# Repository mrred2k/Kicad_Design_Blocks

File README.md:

# KiCad Design Blocks

Stop redrawing the same 3V3 LDO, the same USB-C receptacle and the same buck
converter in every new project.

This repository collects those fragments as **design blocks**: a schematic you drop
into your sheet, plus — where available — the matching PCB layout, with footprints,
values and LCSC part numbers already assigned. Add the repo as a Git submodule, point
KiCad at it, and the blocks show up in the Design Block palette of the Schematic and
PCB editors.

## Requirements

| | |
|---|---|
| **KiCad** | 10.0 or newer. Schematic design blocks arrived in KiCad 9, PCB design blocks in KiCad 10 — this library uses both. |
| **Git** | Anything that supports submodules. |

## Using the blocks in a project

### 1. Add the library once

```bash
git submodule add https://github.com/mrred2k/Kicad_Design_Blocks.git kicad-design-blocks
git commit -m "Add kicad-design-blocks submodule"
```

### 2. Point KiCad at it

**Preferences → Manage Design Block Libraries → Add:**

| Nickname | Path |
|----------|------|
| `blocks` | `${KIPRJMOD}/kicad-design-blocks/blocks.kicad_blocks` |

This writes a `design-block-lib-table` into your project folder — commit it, so the
next person cloning your project gets the same library binding.

### 3. Place a block

Open the **Design Blocks** panel (Schematic Editor, right dock), pick a block, click
the canvas. Most blocks arrive with reference designators already unique-ish and with
hidden power symbols; reconnect `+3V3`, `+5V`, `GND` and the I/O labels to your own
nets.

PCB blocks live in the PCB Editor's Design Blocks panel. Place the schematic part
first, then the layout inside the same project so both stay in sync.

### Clone a project that already uses this library

```bash
git clone --recurse-submodules <project-url>
# already cloned?
git submodule update --init
```

### Pull new blocks into an existing project

```bash
git submodule update --remote kicad-design-blocks
git add kicad-design-blocks
git commit -m "Update kicad-design-blocks"
```

## What is inside a block

```
blocks.kicad_blocks/
└── <BlockName>.kicad_block/
    ├── <BlockName>.kicad_sch    # Schematic fragment
    ├── <BlockName>.kicad_pcb    # PCB layout fragment (optional)
    ├── <BlockName>.json         # Description, keywords, metadata fields
    ├── <BlockName>_preview.svg  # Generated by CI
    └── README.md                # Generated by CI (BOM + badges)
```

The `.json` is the contract: `description` and `keywords` are what KiCad shows in the
block browser, and the metadata fields decide the quality tier
([quality scale](CONTRIBUTING.md#quality-scale)):

| Field | Meaning |
|-------|---------|
| `maturity` | `schematic` → `layout` → `produced` |
| `lcsc_parts` | LCSC part numbers assigned to every component |
| `jlcpcb_basic` | Parts picked from the JLCPCB Basic list where possible |
| `has_3d` | 3D models assigned (`yes` / `partial` / `no`) |
| `reviewed` | Second pair of eyes looked at it |

A **Silver** block is the usual target: layout included, LCSC numbers everywhere, no
JLCPCB Extended-part surcharges.

## Contributing a block

1. In the Schematic Editor: select the circuit → right click → **Save as Design Block**
2. Choose the `blocks` library, fill in name, keywords, description and metadata
3. Optionally save the matching PCB layout as a design block in the PCB Editor
4. Open a pull request

CI then renders your block, posts the preview and a BOM as a PR comment, and flags
metadata problems. Full details: [CONTRIBUTING.md](CONTRIBUTING.md).

## Automation

Nothing in this repo is drawn by hand twice. Three workflows keep it consistent:

| Workflow | Trigger | What it does |
|----------|---------|--------------|
| **Validate design blocks** | PR touching `blocks.kicad_blocks/` | Checks every block has schematic, `.json`, description and valid metadata |
| **PR block preview** | PR touching `blocks.kicad_blocks/` | Renders new/changed blocks, posts preview + BOM + JLCPCB hints as a PR comment |
| **Generate block previews** | push to `main` | Re-renders every block preview and refreshes the per-block README + BOM, commits the result |

## KiCad documentation

- [Schematic design blocks](https://docs.kicad.org/10.0/en/eeschema/eeschema.html#schematic-design-blocks)
- [PCB design blocks](https://docs.kicad.org/10.0/en/pcbnew/pcbnew.html#pcb-design-blocks)

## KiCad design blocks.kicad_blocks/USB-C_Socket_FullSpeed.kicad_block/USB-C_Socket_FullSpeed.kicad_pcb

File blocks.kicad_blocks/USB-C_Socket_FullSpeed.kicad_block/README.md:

<!-- AUTO-GENERATED — do not edit, this file is overwritten on every push to main -->

# USB-C_Socket_FullSpeed

USB 2.0 Type-C receptacle for full-speed devices (HRO TYPE-C-31-M-12), 5.1k pulldowns on CC1/CC2 for 5V sink, 3.6V zener clamps on D+/D-. No 1.5k data pull-up: full-speed devices with an internal pull-up (CH340, RP2040, STM32) connect directly. Socket and ESD are LCSC Extended (no Basic alternative exists in the JLC catalogue); the CC resistors are Basic. Layout included. Superseded by USB-C_Socket_FullSpeed_SRV05, which uses an SRV05-4 array instead of the zeners (roughly 300x lower line capacitance, nanosecond clamping, also protects CC1/CC2); kept as the simpler variant when a zener is acceptable.

## Bill of Materials

*Manufacturer, MPN and JLCPCB class fetched automatically from the [JLCPCB parts API](https://jlcpcb.com/parts).*

| Refs | Value | Footprint | LCSC | JLCPCB | Manufacturer | MPN | Category |
| --- | --- | --- | --- | --- | --- | --- | --- |
| D7, D8 | 3.6V | D_SOD-123 | C22395524 | Extended | hongjiacheng | MM1W3V6 | Zener Diodes |
| J2 | TYPE-C-31-M-12 | USB_C_Receptacle_HRO_TYPE-C-31-M-12 | C165948 | Extended | Korean Hroparts Elec | TYPE-C-31-M-12 | USB Connectors |
| R11, R13 | 5.1k | R_0603_1608Metric | C23186 | Basic | UNI-ROYAL(Uniroyal Elec) | 0603WAF5101T5E | Chip Resistor - Surface Mount |

---
*Keywords: usb usb-c type-c connector full-speed sink cc-resistor esd*

| | |
|---|---|
| Maturity | Layout |
| LCSC Parts | Yes |
| JLCPCB | Optimized for Basic Parts |
| 3D Models | Partial |
| Reviewed | No |

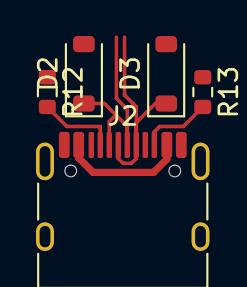
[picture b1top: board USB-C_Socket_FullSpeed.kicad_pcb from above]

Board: 2 copper layers, 5 parts (0 on the bottom side), 6 nets.

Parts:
D2, D3: 3.6V; D_SOD-123
J2: TYPE-C-31-M-12; USB_C_Receptacle_HRO_TYPE-C-31-M-12
R12, R13: 5.1k; R_0603_1608Metric

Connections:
+5V: J2.A4 (VBUS), J2.A9 (VBUS), J2.B4 (VBUS), J2.B9 (VBUS)
GND: D2.2 (A), D3.2 (A), J2.A1 (GND), J2.A12 (GND), J2.B1 (GND), J2.B12 (GND), J2.SH (SHIELD), R12.1, R13.1
unnamed: J2.A5 (CC1), R12.2
unnamed: J2.B5 (CC2), R13.2
USD_D+: D3.1 (K), J2.A6 (D+), J2.B6 (D+)
USD_D-: D2.1 (K), J2.A7 (D-), J2.B7 (D-)

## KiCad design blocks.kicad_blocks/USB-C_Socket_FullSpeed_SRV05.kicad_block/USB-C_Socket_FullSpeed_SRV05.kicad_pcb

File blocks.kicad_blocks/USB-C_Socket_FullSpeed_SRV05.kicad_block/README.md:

<!-- AUTO-GENERATED — do not edit, this file is overwritten on every push to main -->

# USB-C_Socket_FullSpeed_SRV05

USB 2.0 Type-C receptacle (HRO TYPE-C-31-M-12) as a 5V sink for full-speed devices: 5.1k pulldowns on CC1/CC2, ESD array SRV05-4 (SOT-23-6, 0.3 pF, 4 channels) protecting D+, D-, CC1 and CC2, VP tied to VBUS (5V), VN to GND. No 1.5k data pull-up - full-speed devices with an internal pull-up (CH340, RP2040, STM32) connect directly. Preferred over USB-C_Socket_FullSpeed, which uses two 3.6V zeners: the array has roughly 300x lower line capacitance, clamps in nanoseconds instead of microseconds and also protects the CC lines. Socket and ESD array are LCSC Extended (the JLC catalogue has no Basic ESD part); the 5.1k resistors are Basic. Schematic and layout included; the USB-C footprint lives in the project library GnssFanout, so the block is used inside projects of this repo family.

## Bill of Materials

*Manufacturer, MPN and JLCPCB class fetched automatically from the [JLCPCB parts API](https://jlcpcb.com/parts).*

| Refs | Value | Footprint | LCSC | JLCPCB | Manufacturer | MPN | Category |
| --- | --- | --- | --- | --- | --- | --- | --- |
| J2 | TYPE-C-31-M-12 | USB_C_Receptacle_HRO_TYPE-C-31-M-12 | C165948 | Extended | Korean Hroparts Elec | TYPE-C-31-M-12 | USB Connectors |
| R11, R13 | 5.1k | R_0603_1608Metric | C23186 | Basic | UNI-ROYAL(Uniroyal Elec) | 0603WAF5101T5E | Chip Resistor - Surface Mount |
| U6 | SRV05-4 | SOT-23-6 | C558418 | Extended | TECH PUBLIC | SRV05-4 | ESD and Surge Protection (TVS/ESD) |

---
*Keywords: usb usb-c type-c connector full-speed 5v sink cc-resistor esd srv05 tvs*

| | |
|---|---|
| Maturity | Layout |
| LCSC Parts | Yes |
| JLCPCB | Optimized for Basic Parts |
| 3D Models | Yes |
| Reviewed | No |

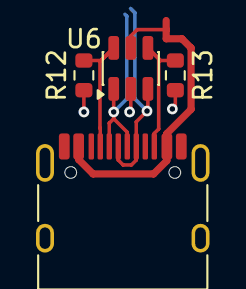
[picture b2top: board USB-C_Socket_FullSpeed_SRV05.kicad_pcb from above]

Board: 2 copper layers, 4 parts (0 on the bottom side), 6 nets.

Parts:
J2: TYPE-C-31-M-12; USB_C_Receptacle_HRO_TYPE-C-31-M-12
R12, R13: 5.1k; R_0603_1608Metric
U6: SRV05-4; SOT-23-6

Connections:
+5V: J2.A4 (VBUS), J2.A9 (VBUS), J2.B4 (VBUS), J2.B9 (VBUS), U6.5 (VP)
CC1: J2.A5 (CC1), R12.2, U6.6 (IO4)
CC2: J2.B5 (CC2), R13.2, U6.4 (IO3)
GND: J2.A1 (GND), J2.A12 (GND), J2.B1 (GND), J2.B12 (GND), J2.SH (SHIELD), R12.1, R13.1, U6.2 (VN)
USD_D+: J2.A6 (D+), J2.B6 (D+), U6.3 (IO2)
USD_D-: J2.A7 (D-), J2.B7 (D-), U6.1 (IO1)

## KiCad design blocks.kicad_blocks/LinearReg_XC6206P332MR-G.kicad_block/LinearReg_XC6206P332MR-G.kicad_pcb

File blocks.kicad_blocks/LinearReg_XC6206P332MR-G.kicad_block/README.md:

<!-- AUTO-GENERATED — do not edit, this file is overwritten on every push to main -->

# LinearReg_XC6206P332MR-G

LDO linear regulator, Vin 5V, Vout 3.3V fixed, 250mA max, XC6206P332MR-G (SOT-23-3)

## Bill of Materials

*Manufacturer, MPN and JLCPCB class fetched automatically from the [JLCPCB parts API](https://jlcpcb.com/parts).*

| Refs | Value | Footprint | LCSC | JLCPCB | Manufacturer | MPN | Category |
| --- | --- | --- | --- | --- | --- | --- | --- |
| C4 | 0.1u 50V | C_0603_1608Metric | C14663 | Basic | YAGEO | CC0603KRX7R9BB104 | Multilayer Ceramic Capacitors MLCC - SMD/SMT |
| C5, C6 | 10uF (50V) | C_1206_3216Metric | C13585 | Basic | Samsung Electro-Mechanics | CL31A106KBHNNNE | Multilayer Ceramic Capacitors MLCC - SMD/SMT |
| U2 | XC6206P332MR-G | SOT-23-3 | C5446 | Basic | Torex Semicon | XC6206P332MR-G | Voltage Regulators - Linear, Low Drop Out (LDO) Regulators |

---
*Keywords: ldo linear regulator 3V3*

| | |
|---|---|
| Maturity | Layout |
| LCSC Parts | Yes |
| JLCPCB | Optimized for Basic Parts |
| 3D Models | Yes |
| Reviewed | No |

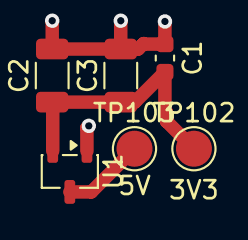
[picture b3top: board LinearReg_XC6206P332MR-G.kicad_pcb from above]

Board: 2 copper layers, 6 parts (0 on the bottom side), 3 nets.

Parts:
C1: 0.1u 50V; C_0603_1608Metric
C2, C3: 10uF (50V); C_1206_3216Metric
TP102: 3V3; TestPoint_Pad_D2.0mm
TP103: 5V; TestPoint_Pad_D2.0mm
U1: XC6206P332MR-G; SOT-23-3

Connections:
+3V3: C1.1, C2.1, C3.1, TP102.1, U1.2 (VO)
+5V: TP103.1, U1.3 (VI)
GND: C1.2, C2.2, C3.2, U1.1 (GND)

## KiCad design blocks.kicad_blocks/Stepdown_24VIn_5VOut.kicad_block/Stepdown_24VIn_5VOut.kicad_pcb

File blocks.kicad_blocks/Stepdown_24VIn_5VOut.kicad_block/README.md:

<!-- AUTO-GENERATED — do not edit, this file is overwritten on every push to main -->

# Stepdown_24VIn_5VOut

Buck (step-down) DC/DC converter, Vin max 32V, Vout fixed 5V

## Bill of Materials

*Manufacturer, MPN and JLCPCB class fetched automatically from the [JLCPCB parts API](https://jlcpcb.com/parts).*

| Refs | Value | Footprint | LCSC | JLCPCB | Manufacturer | MPN | Category |
| --- | --- | --- | --- | --- | --- | --- | --- |
| C406 | 0.1u 50V | C_0603_1608Metric | C14663 | Basic | YAGEO | CC0603KRX7R9BB104 | Multilayer Ceramic Capacitors MLCC - SMD/SMT |
| C407 | 100uF 35V | CP_Elec_6.3x5.4 | C2836442 | Extended | KNSCHA | RVT100UF35V67RV0034 | Aluminum Electrolytic Capacitors - SMD |
| C408 | 10uF (50V) | C_1206_3216Metric | C13585 | Basic | Samsung Electro-Mechanics | CL31A106KBHNNNE | Multilayer Ceramic Capacitors MLCC - SMD/SMT |
| C409, C410 | 47uF (10V) | C_1206_3216Metric_Pad1.33x1.80mm_HandSolder | C96123 | Basic | Samsung Electro-Mechanics | CL31A476MPHNNNE | Multilayer Ceramic Capacitors MLCC - SMD/SMT |
| L402 | 4.7uH | L_Sunlord_MWSA0503S | C177246 | Extended | cjiang (Changjiang Microelectronics Tech) | FXL0530-4R7-M | Molding Power Inductors |
| U402 | AP63205WU-7 | TSOT-23-6 | C2071056 | Extended | Diodes Incorporated | AP63205WU-7 | DC-DC Converters |

---
*Keywords: buck step-down dcdc converter 5V power*

| | |
|---|---|
| Maturity | Layout |
| LCSC Parts | Yes |
| JLCPCB | Optimized for Basic Parts |
| 3D Models | Yes |
| Reviewed | No |

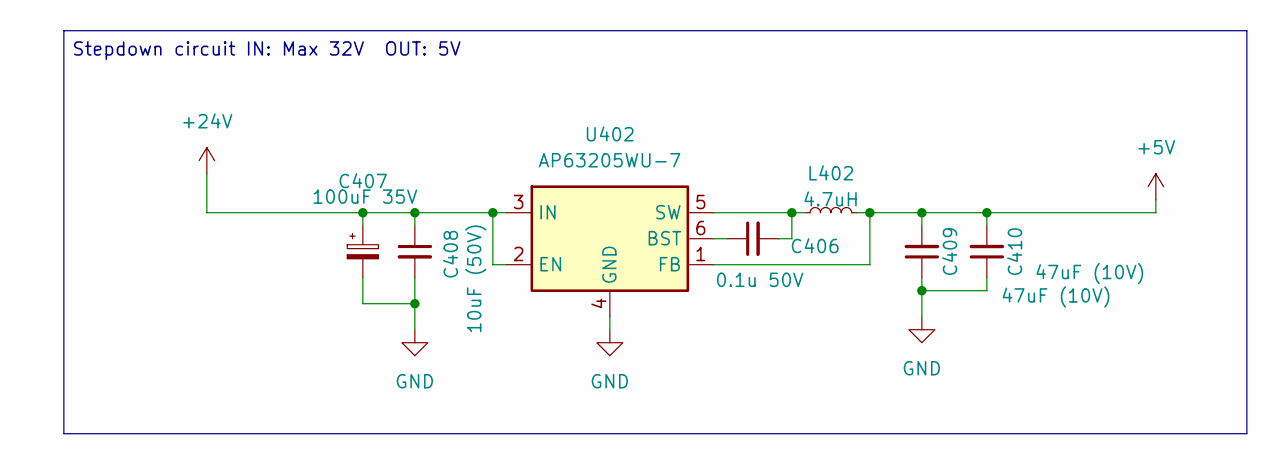
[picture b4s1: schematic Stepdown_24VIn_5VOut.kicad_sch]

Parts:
C406: 0.1u 50V; C_0603_1608Metric; LCSC C14663
C407: 100uF 35V; CP_Elec_6.3x5.4; LCSC C2836442
C408: 10uF (50V); C_1206_3216Metric; LCSC C13585
C409, C410: 47uF (10V); C_1206_3216Metric_Pad1.33x1.80mm_HandSolder; LCSC C96123
L402: 4.7uH; L_Sunlord_MWSA0503S; LCSC C177246
U402: AP63205WU-7; TSOT-23-6; LCSC C2071056

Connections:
+5V: C409.2, C410.2, L402.2, U402.1 (FB)
+24V: C407.1, C408.1, U402.2 (EN), U402.3 (IN)
GND: C407.2, C408.2, C409.1, C410.1, U402.4 (GND)
unnamed: C406.1, U402.6 (BST)
unnamed: C406.2, L402.1, U402.5 (SW)

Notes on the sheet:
Stepdown circuit IN: Max 32V OUT: 5V

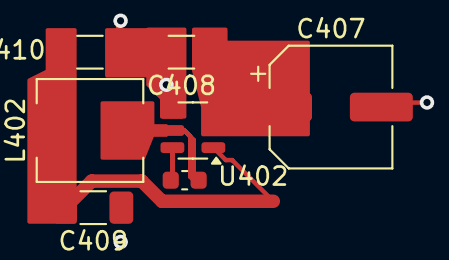
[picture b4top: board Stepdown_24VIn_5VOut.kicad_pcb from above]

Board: 2 copper layers, 7 parts (0 on the bottom side), 5 nets.

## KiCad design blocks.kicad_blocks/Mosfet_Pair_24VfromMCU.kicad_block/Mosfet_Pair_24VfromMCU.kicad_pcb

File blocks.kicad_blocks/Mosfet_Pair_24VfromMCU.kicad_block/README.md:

<!-- AUTO-GENERATED — do not edit, this file is overwritten on every push to main -->

# Mosfet_Pair_24VfromMCU

Low-side switch for 24V loads, BJT-driven N-ch MOSFET (AO3400A), active high, MCU-compatible input, status LED included

## Bill of Materials

*Manufacturer, MPN and JLCPCB class fetched automatically from the [JLCPCB parts API](https://jlcpcb.com/parts).*

| Refs | Value | Footprint | LCSC | JLCPCB | Manufacturer | MPN | Category |
| --- | --- | --- | --- | --- | --- | --- | --- |
| D204 | red | LED_0603_1608Metric | C2286 | Basic | Hubei KENTO Elec | KT-0603R | LED Indication - Discrete |
| Q207 | AO3400A | SOT-23 | C20917 | Basic | Alpha & Omega Semicon | AO3400A | MOSFETs |
| Q210, Q210 | MBT3904DW1 | SOT-363_SC-70-6 | C110150 | Extended | onsemi | MBT3904DW1T1G | Bipolar (BJT) |
| R206, R213 | 10k | R_0603_1608Metric | C25804 | Basic | UNI-ROYAL(Uniroyal Elec) | 0603WAF1002T5E | Chip Resistor - Surface Mount |
| R212, R221 | 1k | R_0603_1608Metric | C21190 | Basic | UNI-ROYAL(Uniroyal Elec) | 0603WAF1001T5E | Chip Resistor - Surface Mount |

---
*Keywords: mosfet mcu low-side switching*

| | |
|---|---|
| Maturity | Produced |
| LCSC Parts | Yes |
| JLCPCB | Optimized for Basic Parts |
| 3D Models | Yes |
| Reviewed | No |

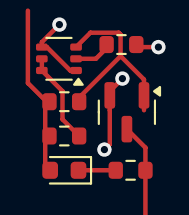
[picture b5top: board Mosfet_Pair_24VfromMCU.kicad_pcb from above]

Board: 2 copper layers, 7 parts (0 on the bottom side), 7 nets.

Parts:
D201: red; LED_0603_1608Metric
Q201: AO3400A; SOT-23
Q204: MBT3904DW1; SOT-363_SC-70-6
R201, R231: 10k; R_0603_1608Metric
R207, R210: 1k; R_0603_1608Metric

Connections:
+24V: D201.2 (A), R201.2, R231.2
GND: Q201.2 (S), Q204.1 (E1), Q204.4 (E2)
unnamed: D201.1 (K), R207.2
unnamed: Q201.1 (G), Q204.3 (C2), R201.1
unnamed: Q204.2 (B1), R210.2
unnamed: Q204.5 (B2), Q204.6 (C1), R231.1
Output_01: Q201.3 (D), R207.1

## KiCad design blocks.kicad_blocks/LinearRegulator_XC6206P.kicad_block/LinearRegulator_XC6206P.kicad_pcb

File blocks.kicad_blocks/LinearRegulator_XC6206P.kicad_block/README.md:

<!-- AUTO-GENERATED — do not edit, this file is overwritten on every push to main -->

# LinearRegulator_XC6206P

LDO linear regulator, Vin 5V, Vout 3.3V fixed, 250mA max, XC6206P (SOT-23-3)

## Bill of Materials

*Manufacturer, MPN and JLCPCB class fetched automatically from the [JLCPCB parts API](https://jlcpcb.com/parts).*

| Refs | Value | Footprint | LCSC | JLCPCB | Manufacturer | MPN | Category |
| --- | --- | --- | --- | --- | --- | --- | --- |
| C9, C10 | 1u 50V | C_0603_1608Metric | C15849 | Basic | Samsung Electro-Mechanics | CL10A105KB8NNNC | Multilayer Ceramic Capacitors MLCC - SMD/SMT |
| U2 | XC6206PxxxMR | SOT-23-3 | C5446 | Basic | Torex Semicon | XC6206P332MR-G | Voltage Regulators - Linear, Low Drop Out (LDO) Regulators |

---
*Keywords: ldo linear regulator 3V3 XC6206*

| | |
|---|---|
| Maturity | Layout |
| LCSC Parts | Yes |
| JLCPCB | Optimized for Basic Parts |
| 3D Models | Yes |
| Reviewed | No |

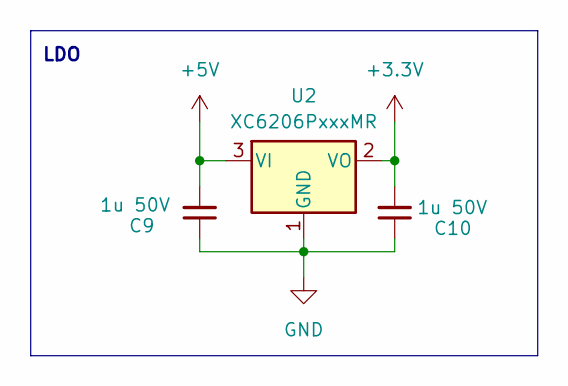
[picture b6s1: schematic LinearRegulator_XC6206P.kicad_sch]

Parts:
C9, C10: 1u 50V; C_0603_1608Metric; LCSC C15849
U2: XC6206PxxxMR; SOT-23-3; LCSC C5446

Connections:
+3.3V: C10.2, U2.2 (VO)
+5V: C9.2, U2.3 (VI)
GND: C9.1, C10.1, U2.1 (GND)

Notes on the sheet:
LDO

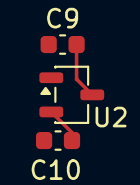
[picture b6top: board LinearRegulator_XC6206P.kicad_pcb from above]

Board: 2 copper layers, 3 parts (0 on the bottom side), 3 nets.

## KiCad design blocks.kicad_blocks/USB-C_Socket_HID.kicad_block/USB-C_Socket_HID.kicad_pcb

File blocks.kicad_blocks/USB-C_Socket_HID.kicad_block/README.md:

<!-- AUTO-GENERATED — do not edit, this file is overwritten on every push to main -->

# USB-C_Socket_HID

USB 2.0 Type-C receptacle, low-speed HID device, CC resistors for 5V power negotiation, ESD protection on D+/D-

## Bill of Materials

*Manufacturer, MPN and JLCPCB class fetched automatically from the [JLCPCB parts API](https://jlcpcb.com/parts).*

| Refs | Value | Footprint | LCSC | JLCPCB | Manufacturer | MPN | Category |
| --- | --- | --- | --- | --- | --- | --- | --- |
| D7, D8 | 3.6V | D_SOD-123 | C22395524 | Extended | hongjiacheng | MM1W3V6 | Zener Diodes |
| J10 | USB_C_Receptacle_USB2.0_16P | USB_C_SMD_allpin_Aliexpress | C2681552 | Extended | SHOU HAN | TYPE-C 16P QTGM027 | USB Connectors |
| R11, R13 | 5.1k | R_0603_1608Metric | C23186 | Basic | UNI-ROYAL(Uniroyal Elec) | 0603WAF5101T5E | Chip Resistor - Surface Mount |
| R12 | 1.5k | R_0603_1608Metric | C22843 | Basic | UNI-ROYAL(Uniroyal Elec) | 0603WAF1501T5E | Chip Resistor - Surface Mount |
| R14, R15 | 47 | R_0603_1608Metric | C23182 | Basic | UNI-ROYAL(Uniroyal Elec) | 0603WAF470JT5E | Chip Resistor - Surface Mount |

---
*Keywords: usb usb-c connector hid tinyusb*

| | |
|---|---|
| Maturity | Produced |
| LCSC Parts | Yes |
| JLCPCB | Optimized for Basic Parts |
| 3D Models | Yes |
| Reviewed | No |

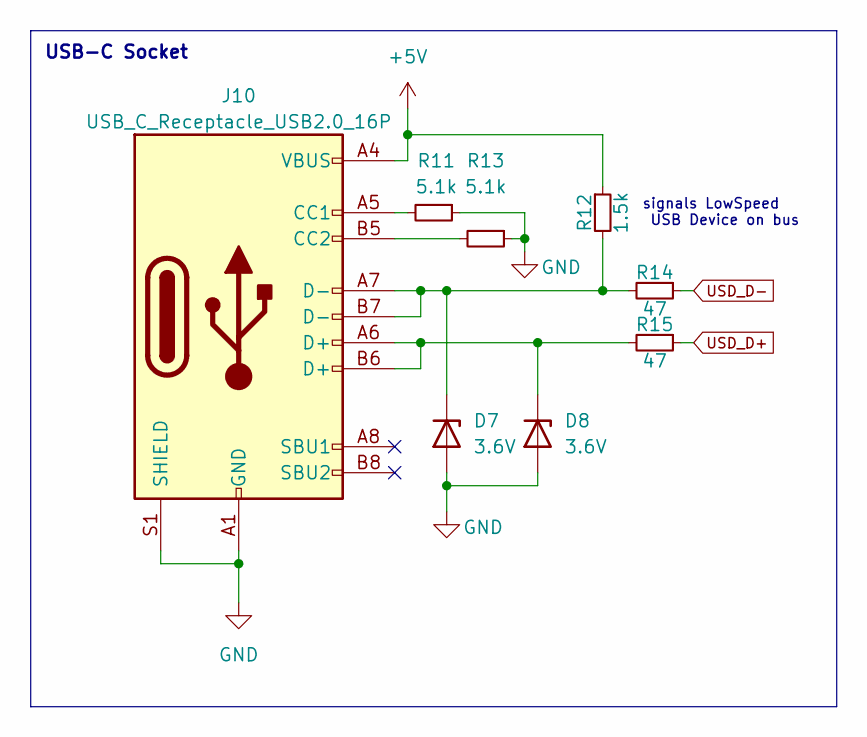
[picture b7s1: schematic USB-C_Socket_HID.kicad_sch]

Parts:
D7, D8: 3.6V; D_SOD-123; LCSC C22395524
J10: USB_C_Receptacle_USB2.0_16P; USB_C_SMD_allpin_Aliexpress; LCSC C2681552
R11, R13: 5.1k; R_0603_1608Metric; MPN 0603WAF100JT5E; LCSC C23186
R12: 1.5k; R_0603_1608Metric; MPN 0603WAF100JT5E; LCSC C22843
R14, R15: 47; R_0603_1608Metric; MPN 0603WAF100JT5E; LCSC C23182

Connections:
+5V: J10.A4 (VBUS), J10.A9 (VBUS), J10.B4 (VBUS), J10.B9 (VBUS), R12.1
GND: D7.2 (A), D8.2 (A), J10.A1 (GND), J10.A12 (GND), J10.B1 (GND), J10.B12 (GND), J10.S1 (SHIELD), R11.1, R13.1
unnamed: D7.1 (K), J10.A7 (D-), J10.B7 (D-), R12.2, R14.2
unnamed: D8.1 (K), J10.A6 (D+), J10.B6 (D+), R15.2
unnamed: J10.A5 (CC1), R11.2
unnamed: J10.B5 (CC2), R13.2
USD_D+: R15.1
USD_D-: R14.1

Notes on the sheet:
USB-C Socket
signals LowSpeed USB Device on bus

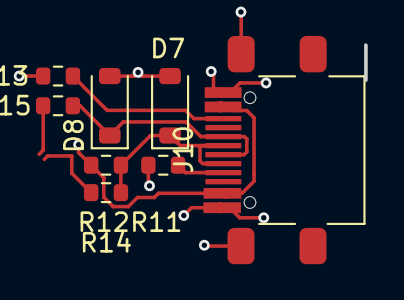
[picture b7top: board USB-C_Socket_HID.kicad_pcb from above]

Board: 2 copper layers, 8 parts (0 on the bottom side), 6 nets.

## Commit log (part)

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2026-06-16 Initial repository setup
    Add README with submodule usage instructions, CONTRIBUTING with block naming conventions and metadata field schema, and .gitignore for KiCad backup files.
2026-06-16 Add initial design blocks
    Add 7 blocks: Stepdown_24VIn_5VOut, Mosfet_Pair_24VfromMCU, LinearReg_XC6206P332MR-G, LinearRegulator_AMS1117, LinearRegulator_AP2204K, LinearRegulator_XC6206P, USB-C_Socket_HID. Each block includes 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
2026-06-17 feat: CI workflows -- SVG previews, BOM, PR comments, README auto-generation
2026-06-17 feat: quality tier badges (Wood/Bronze/Silver/Gold/Platinum) with documentation
2026-06-17 feat: enrich BOM with LCSC manufacturer, MPN, category and JLCPCB class
2026-06-17 chore: regenerate block previews
2026-06-17 nicer layout
2026-06-17 fix: translate PR template to English, fix jlcpcb_basic field name
2026-06-17 fix: only flag README.md if it is new in the PR, not already on main
2026-06-17 fix: remove unnecessary pull before force-push to preview branch
2026-06-17 fix: pr preview comment shows only changed blocks, not all
2026-06-17 nicer layout (#1)
    * nicer layout
    * fix: translate PR template to English, fix jlcpcb_basic field name
    * fix: only flag README.md if it is new in the PR, not already on main
    * fix: pr preview comment shows only changed blocks, not all
2026-06-18 feat: hint in PR comment when most parts are JLCPCB Basic but field not set
